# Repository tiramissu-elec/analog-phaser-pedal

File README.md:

# analog-phaser-pedal
Analog phaser guitar pedal with a custom PCB designed in KiCad.
See more details in [Project Notes](project_notes.md)

## Files

- KiCad schematic
- PCB layout
- Example PCB render
- custom 3pdt footswitch footprint

## Tools

- KiCad 9
- Through-hole components

## Notes

This was one of my first PCB layouts. Possible improvements:

- LED replacement from SMT to THT
- trace routing optimization
- switching noise reduction when engaging bypass

## Schematic

## PCB Layout

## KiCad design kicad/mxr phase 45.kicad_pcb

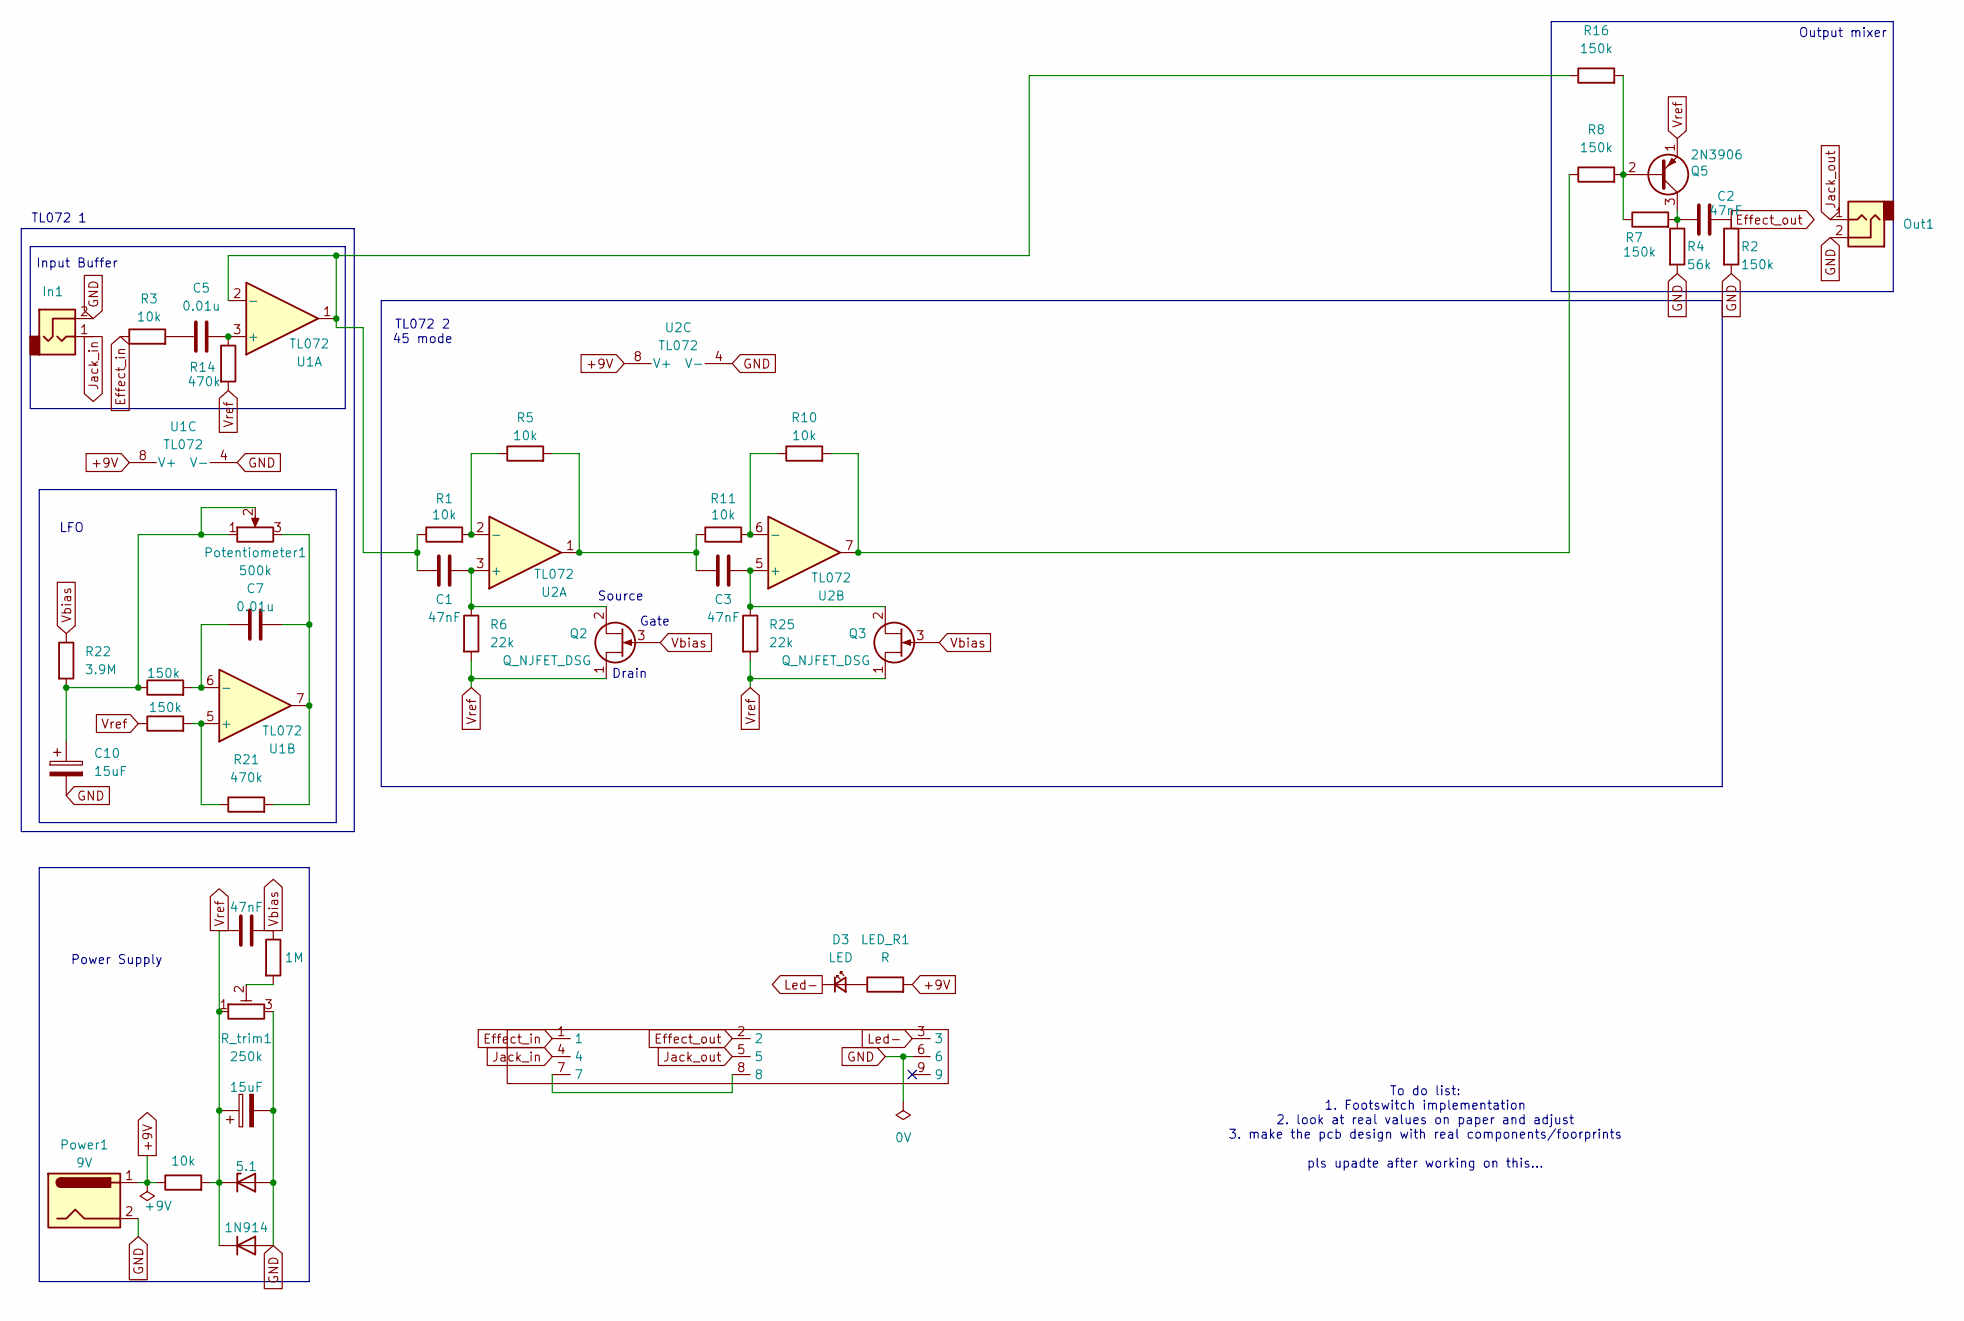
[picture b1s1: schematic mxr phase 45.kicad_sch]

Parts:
C1, C2, C3, C4: 47nF; C_Axial_L3.8mm_D2.6mm_P7.50mm_Horizontal
C5, C7: 0.01u; C_Axial_L3.8mm_D2.6mm_P7.50mm_Horizontal
C8, C10: 15uF; CP_Radial_D7.5mm_P2.50mm
D1: 1N914; D_DO-35_SOD27_P7.62mm_Horizontal
D2: 5.1; D_DO-41_SOD81_P7.62mm_Horizontal
D3: LED; LED_0603_1608Metric
In1: AudioJack2; PinHeader_1x02_P2.54mm_Vertical
LED_R1: R; R_Axial_DIN0207_L6.3mm_D2.5mm_P7.62mm_Horizontal
Out1: AudioJack2; PinHeader_1x02_P2.54mm_Vertical
Potentiometer1: 500k; PinHeader_1x03_P2.54mm_Vertical
Power1: 9V; PinHeader_1x02_P2.54mm_Vertical
Q2, Q3: Q_NJFET_DSG; PinHeader_1x03_P2.54mm_Vertical
Q5: 2N3906; TO-92_Inline
R1, R3, R5, R10, R11, R15: 10k; R_Axial_DIN0207_L6.3mm_D2.5mm_P7.62mm_Horizontal
R2, R7, R8, R16, R19, R24: 150k; R_Axial_DIN0207_L6.3mm_D2.5mm_P10.16mm_Horizontal
R4: 56k; R_Axial_DIN0207_L6.3mm_D2.5mm_P10.16mm_Horizontal
R6, R25: 22k; R_Axial_DIN0207_L6.3mm_D2.5mm_P7.62mm_Horizontal
R14, R21: 470k; R_Axial_DIN0207_L6.3mm_D2.5mm_P10.16mm_Horizontal
R20: 1M; R_Axial_DIN0207_L6.3mm_D2.5mm_P7.62mm_Horizontal
R22: 3.9M; R_Axial_DIN0207_L6.3mm_D2.5mm_P10.16mm_Horizontal
R_trim1: 250k; Potentiometer_Piher_PT-6-V_Vertical
U1, U2: TL072; DIP-8_W7.62mm_Socket
U3: 3PDT_footswitch

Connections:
+9V: LED_R1.2, Power1.1, R15.1, U1.8 (V+), U2.8 (V+)
Effect_in: R3.1, U3.1
Effect_out: C2.2, R2.1, U3.2
GND: C8.2, C10.2, D1.2 (A), D2.2 (A), In1.2, Out1.2, Power1.2, R2.2, R4.2, R_trim1.3, U1.4 (V-), U2.4 (V-), U3.6
Jack_in: In1.1, U3.4
Jack_out: Out1.1, U3.5
Led-: D3.1 (K), U3.3
unnamed: C3.1, R5.2, R11.1, U2.1
unnamed: C5.1, R3.2
unnamed: C7.2, Potentiometer1.3, R21.2, U1.7
unnamed: C10.1, Potentiometer1.1, Potentiometer1.2, R22.2, R24.1
unnamed: D3.2 (A), LED_R1.1
unnamed: C1.2, Q2.2 (S), R6.1, U2.3 (+)
unnamed: C3.2, Q3.2 (S), R25.1, U2.5 (+)
unnamed: Q5.2 (B), R7.1, R8.2, R16.2
unnamed: C2.1, Q5.3 (C), R4.1, R7.2
unnamed: R8.1, R10.2, U2.7
unnamed: R20.2, R_trim1.2
unnamed: C5.2, R14.1, U1.3 (+)
unnamed: C1.1, R1.1, R16.1, U1.1, U1.2 (-)
unnamed: R19.2, R21.1, U1.5 (+)
unnamed: C7.1, R24.2, U1.6 (-)
unnamed: R1.2, R5.1, U2.2 (-)
unnamed: R10.1, R11.2, U2.6 (-)
unnamed: U3.7, U3.8
Vbias: C4.2, Q2.3 (G), Q3.3 (G), R20.1, R22.1
Vref: C4.1, C8.1, D1.1 (K), D2.1 (K), Q2.1 (D), Q3.1 (D), Q5.1 (E), R6.2, R14.2, R15.2, R19.1, R25.2, R_trim1.1

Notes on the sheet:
Drain
TL072 1
Output mixer
Input Buffer
LFO
TL072 2 45 mode
To do list: 1. Footswitch implementation 2. look at real values on paper and adjust 3. make the pcb design with real components/foorprints pls upadte after working on this...
Power Supply
Gate
Source

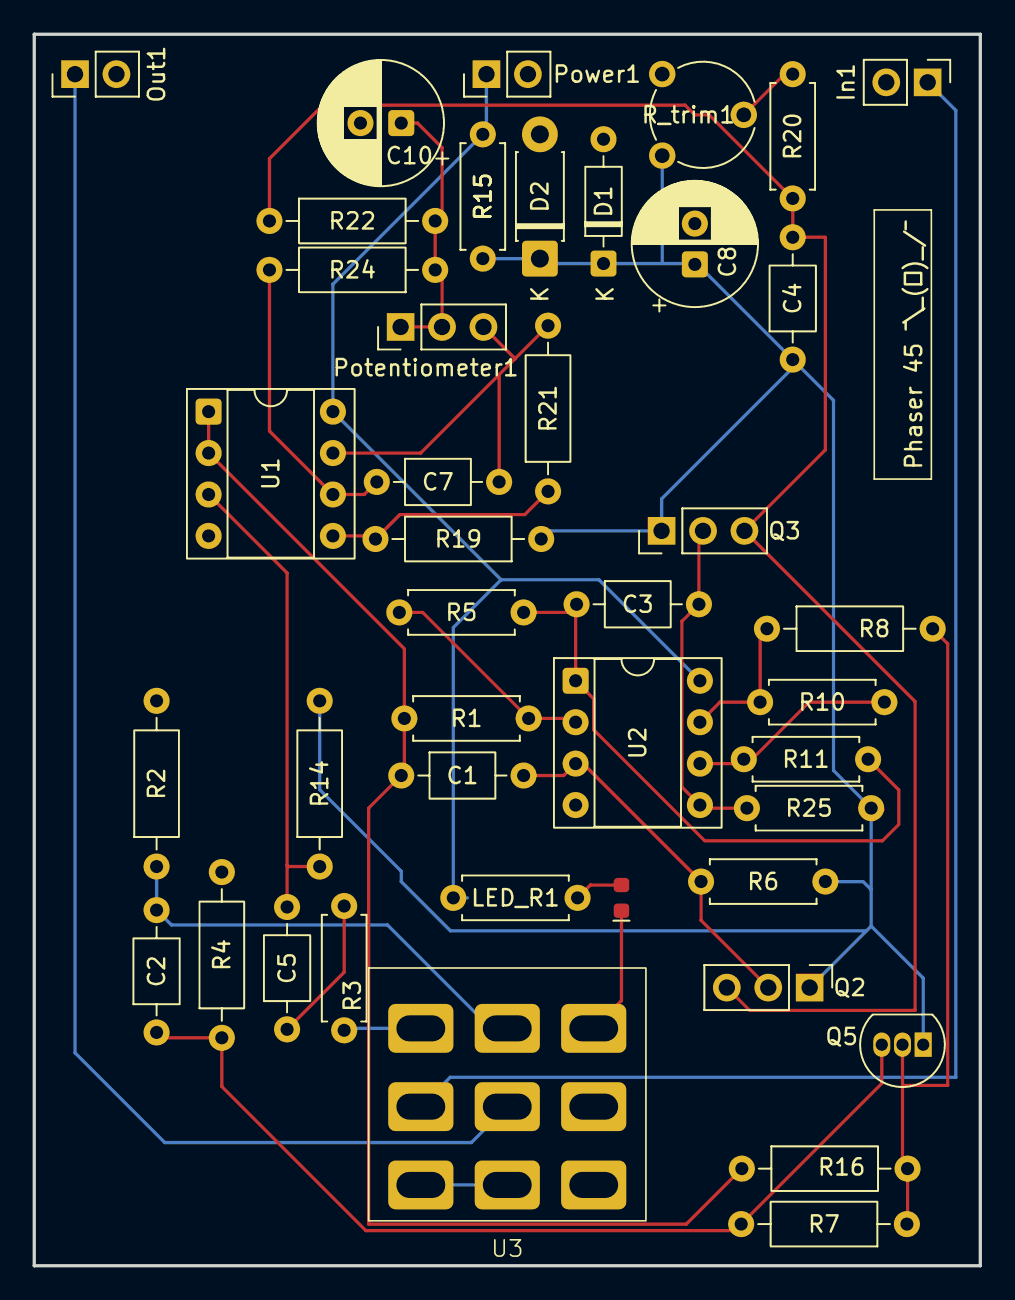
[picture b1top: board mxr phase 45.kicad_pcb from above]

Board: 2 copper layers, 58.0 x 75.5 mm, 42 parts (0 on the bottom side), 27 nets.

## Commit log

2026-04-01 MXR Phase 45 phaser PCB project
    KiCad schematic and PCB design for ananalog phaser pedal inspired by the MXR Phase 90.
2026-04-01 Add files via upload
    Add Gerber fabrication files
2026-04-01 Add files via upload
    Add PCB topalyer picture.
2026-04-01 Rename image.png to PCB.png
2026-04-01 Add files via upload
    Add schematic picture.
2026-04-01 Rename image.png to Schematic.png
2026-04-01 Rename PCB.png to images/PCB.png
2026-04-01 Rename Schematic.png to images/Schematic.png
2026-04-01 Rename mxr phase 45.kicad_pcb to kicad/mxr phase 45.kicad_pcb
2026-04-01 Rename mxr phase 45.kicad_pro to kicad/mxr phase 45.kicad_pro
2026-04-01 Rename mxr phase 45.kicad_sch to kicad/mxr phase 45.kicad_sch
2026-04-01 Create project_notes
    Adds a short documentation of the project.
2026-04-01 Rename docs/project_notes to project_notes
2026-04-01 Rename project_notes to project_notes.md
2026-04-01 Rename mxr phase 45.kicad_pcb to mxr_phase_45.kicad_pcb
2026-04-01 Rename mxr phase 45.kicad_sch to mxr_phase_45.kicad_sch
2026-04-01 Rename mxr phase 45.kicad_pro to mxr_phase_45.kicad_pro
2026-04-01 Add files via upload
    Added custom footprint for 3pdt switch.
2026-04-01 Rename 3pdt_footswitch.pretty/3PDT_footswitch.kicad_mod to libraries/3pdt_footswitch.pretty/3PDT_footswitch.kicad_mod
